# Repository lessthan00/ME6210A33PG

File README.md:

# ME6210A33PG borad change from AMS1117-3V3

[ME6210A33PG](https://www.jlc-smt.com/lcsc/detail?componentCode=C85233)  
LDO  
VIN 18V  
VOUT 3.3V  
IOUT 500mA  
package SOT-89-3  
IQ 2.5uA  
VD 260mV@200mA  

引脚定义  
1-GND  
2-VIN  
3-VOUT  

## HT7550-1 board = ME6210A33PG  

[HT7550-1](https://www.jlc-smt.com/lcsc/detail?componentCode=C5346140)
LDO  
VIN 28V  
VOUT 5V  
IOUT 150mA  
package SOT-89-3
accuracy 2%
IQ 4uA
VD 520mA@100mA  

引脚定义  
1-GND  
2-IN  
3-VOUT 

## RT9013-33GB

[RT9013-33GB](https://www.jlc-smt.com/lcsc/detail?componentCode=C47773)  
LDO  
VIN 5.5V  
VOUT 3.3V  
IOUT 0.5A  
package SOT-23-5  
accuracy 2%  
IQ 50uA  
VD 250mV@500mA  
ENL 0.6V  
ENH 1.6V  
IEN 0.1uA -> 100K电阻  
  
引脚定义  
1-VIN  
2-GND  
3-EN  
4-NC  
5-VOUT  

## ME6211C33M5G-N board = RT9013-33GB  

[ME6211C33M5G-N](https://www.jlc-smt.com/lcsc/detail?componentCode=C82942)  
LDO  
VIN 6V  
VOUT 3.3V  
IOUT 300mA  
package SOT-23-5  
accuracy 2%  
IQ 60uA  
VD 260mV@200mA  
ENL 0.5V  
ENH 1V  
IEN 应该是uA -> 100K电阻  
Vn 50uVrms  
  
引脚定义  
1-VIN  
2-GND  
3-EN  
4-NC  
5-VOUT  

## ME6206A33XG  borad change from AMS1117-3V3
  
[ME6206A33XG](https://www.jlc-smt.com/lcsc/detail?componentCode=C161345)  
LDO  
VIN 6V  
VOUT 3.3V  
IOUT 300mA  
package SOT-23-3  
IQ 8uA  
VD 400mV@200mA  

引脚定义  
1-GND  
2-VOUT  
3-VIN  

kciad 并无其符号, 根据封装和引脚定义, 选择自MCP1703Ax-330xxTT 这个符号派生  
封装也是取其 Package_TO_SOT_SMD:SOT-23  
输入TVS 改为 SMAJ6.0CA  

## AMS1117-3V3  borad change from HT7333
  
[AMS1117-3V3](https://www.jlc-smt.com/lcsc/detail?componentCode=C5120765)  
LDO  
  
VIN 18V  
VOUT 3.3V  
IOUT 1A  
package SOT-223  
IQ 12mA  
VD 1.4V@1A  
  
引脚引脚定义  
  
1 GND  
2 VOUT  
3 VIN  

输入TVS 改为SMAJ18CA
  
## HT7333  
  
[HT7333](https://item.szlcsc.com/323851.html?fromZone=s_s__%2522HT7333%2522&spm=sc.gb.xh2.zy.n___sc.hm.hd.ss&lcsc_vid=EwQKBQVXRFYIBQVTR1JbVFcAFgRYUl0AFFNZVAEARVQxVlNSQVZWVVFfRVBZXzsOAxUeFF5JWBYZEEoEHg8JSQcJGk4%3D)  
  
LDO  
  
VIN 12V  
VOUT 3.3V  
IOUT 250mA  
package SOT-89-3  
IQ 3uA  
VD 90mV@40mA  
  
引脚定义  
  
1 GND  
2 VIN  
3 VOUT  
  
所以使用kciad 里面的 Regulator_Generic_GND_IN_OUT 生成符号  
  
封装采用PCM_Package_TO_SOT_SMD_AKL:SOT-89-3, 已确认封装焊盘顺序定义无误  
  
## TLV70450DBVR  
  
[TLV70450DBVR](https://www.jlc-smt.com/lcsc/detail?componentCode=C91672)  
VIN 24V  
VOUT 5V  
IOUT 150mA  
IQ 4.5uA  
VD 1.1V@100mA  
package SOT-23-5  
  
1-GND  
2-IN  
3-OUT  
4-NC  
5-NC  
  
这样的封装的引脚定义是很少的,基本上只有TLV70450DBVR,甚至需要自己绘制封装...

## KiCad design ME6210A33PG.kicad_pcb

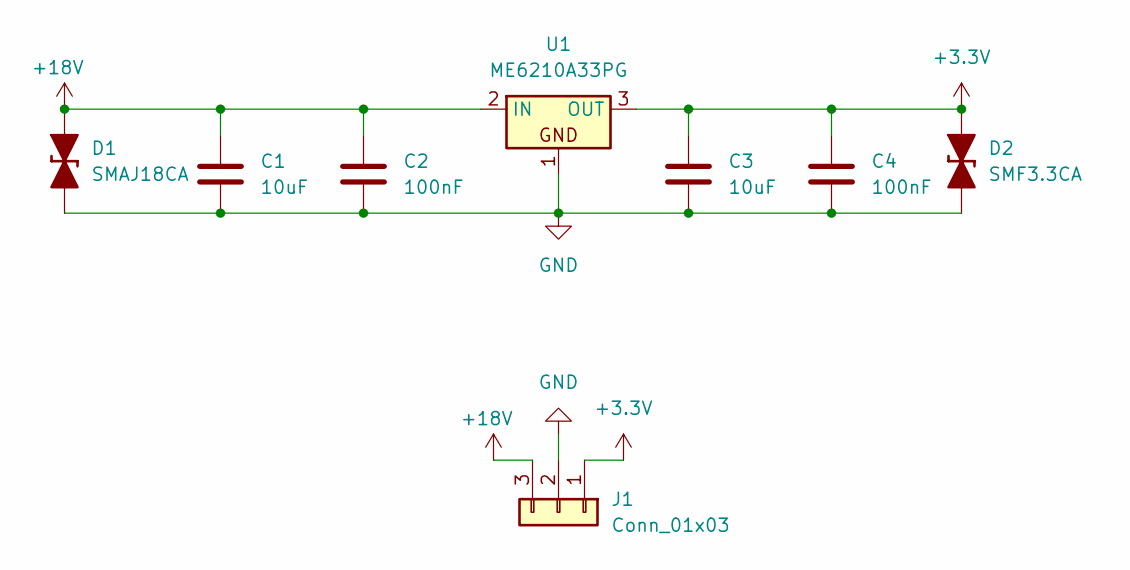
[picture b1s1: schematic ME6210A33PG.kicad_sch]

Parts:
C1, C3: 10uF; C_1206_3216Metric
C2, C4: 100nF; C_1206_3216Metric
D1: SMAJ18CA; D_SMA_TVS
D2: SMF3.3CA; D_SOD-123F
J1: Conn_01x03; PinHeader_1x03_P2.54mm_Vertical
U1: ME6210A33PG; SOT-89-3_BigPads

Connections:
+3.3V: C3.1, C4.1, D2.2 (A), J1.1, U1.3 (OUT)
+18V: C1.1, C2.1, D1.2 (A), J1.3, U1.2 (IN)
GND: C1.2, C2.2, C3.2, C4.2, D1.1 (K), D2.1 (K), J1.2, U1.1

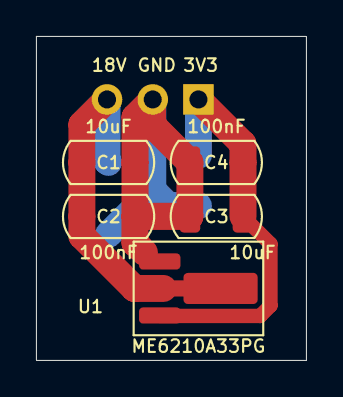
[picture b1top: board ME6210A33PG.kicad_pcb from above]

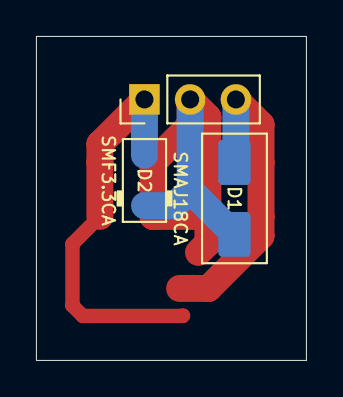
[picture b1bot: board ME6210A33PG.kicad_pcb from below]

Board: 2 copper layers, 15.0 x 18.0 mm, 8 parts (3 on the bottom side), 3 nets.
